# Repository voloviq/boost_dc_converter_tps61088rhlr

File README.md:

# boost_dc_converter_tps61088rhlr

Development Board of TPS61088 Boost DC-DC Converter

Board 3D view

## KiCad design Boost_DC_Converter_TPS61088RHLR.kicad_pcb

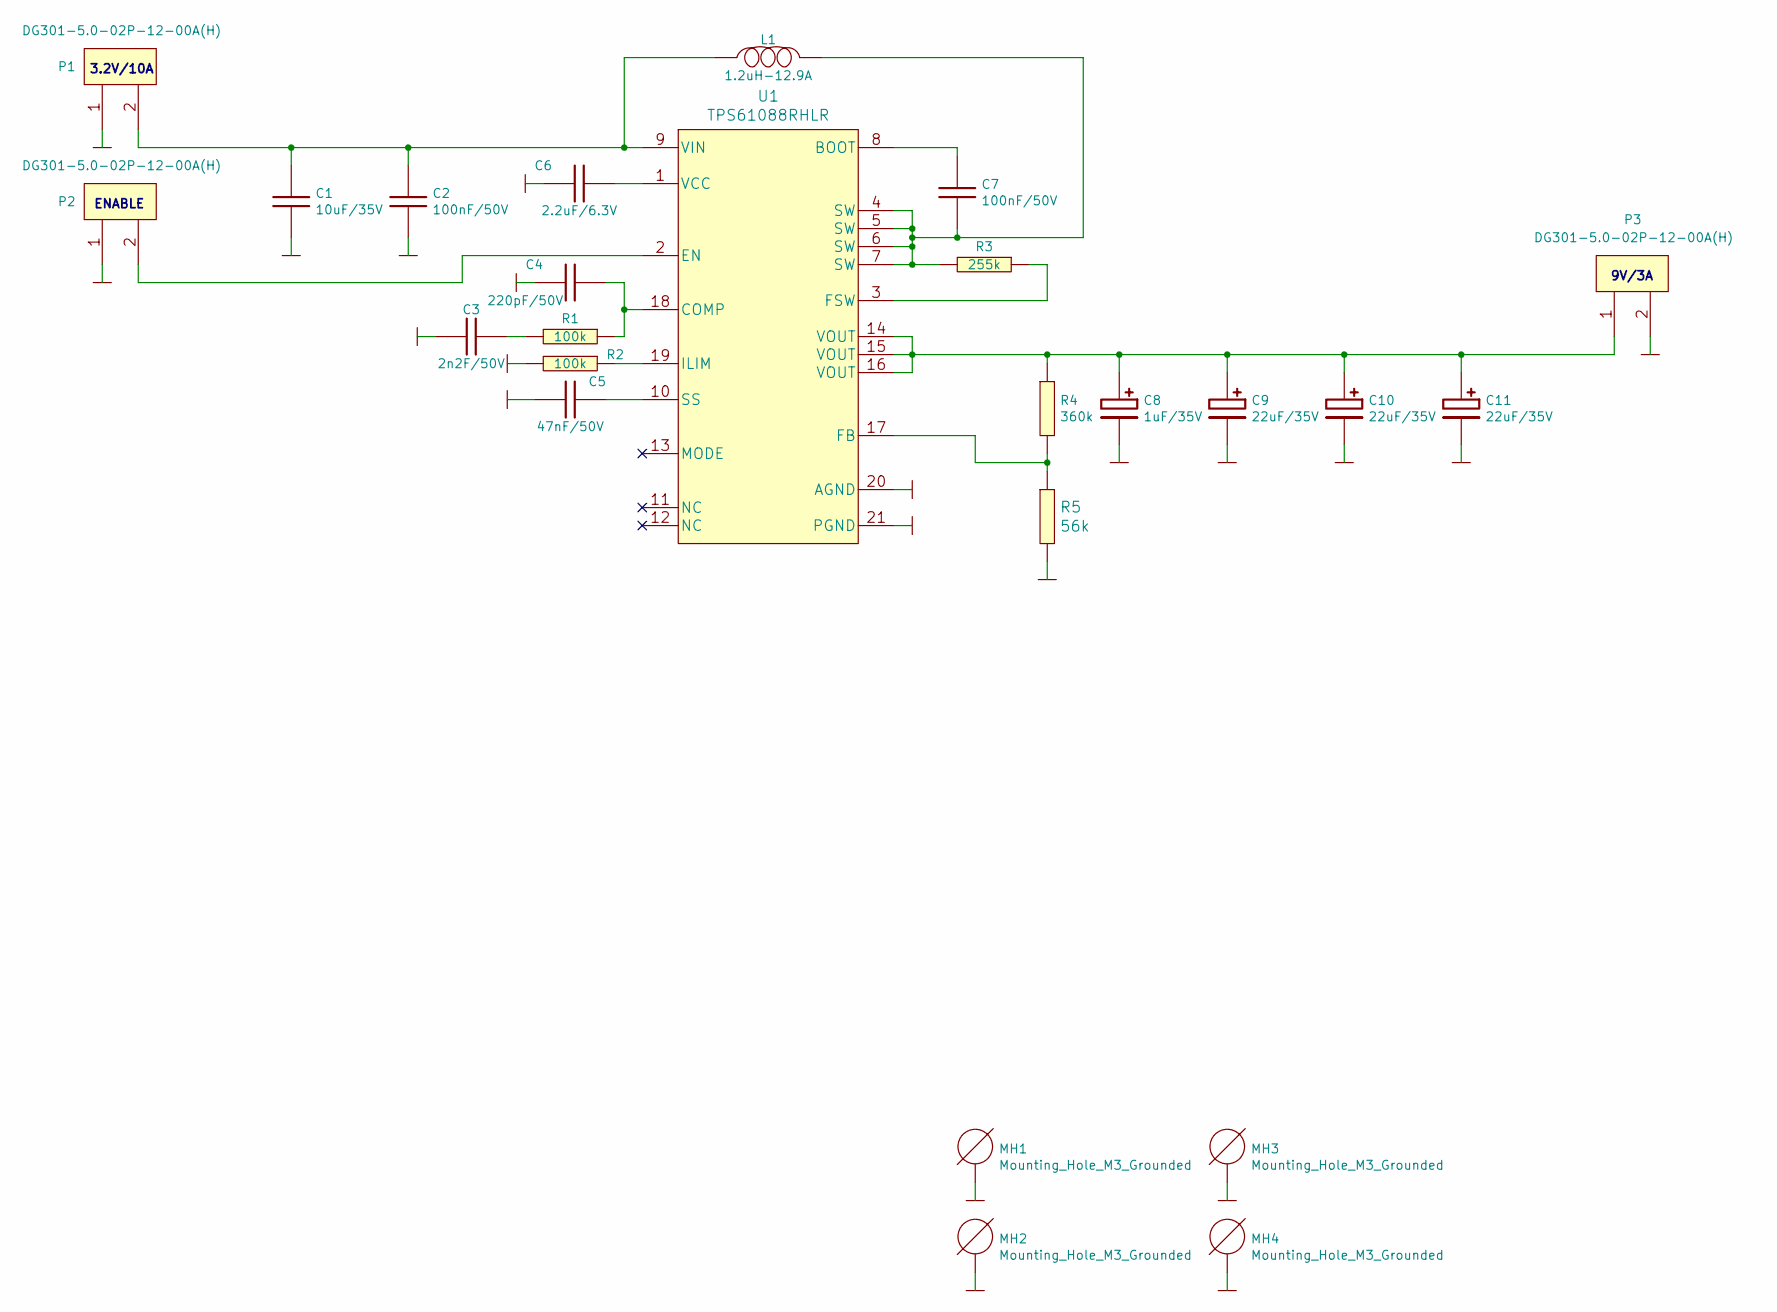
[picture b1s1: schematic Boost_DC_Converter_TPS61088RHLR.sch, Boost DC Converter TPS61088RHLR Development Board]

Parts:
C1: 10uF/35V; 10uF_35V_X7R_1210; Manufacturer Part Number CL32B106KLULNNE
C2, C7: 100nF/50V; 100nF_0603; Manufacturer Part Number CL10B104JB8NNNC
C3: 2n2F/50V; 2.2nF_0603; Manufacturer Part Number GRM1885C1H222JA01D
C4: 220pF/50V; 220pF_0603; Manufacturer Part Number 06035A221JAT2A; LCSC Part # (optional) C431002
C5: 47nF/50V; 47nF_0603; Manufacturer Part Number 0603B473K500CT; LCSC Part # (optional) C313102
C6: 2.2uF/6.3V; 2_2uF_0603
C8: 1uF/35V; 1uF_35V_B_Tantal
C9, C10, C11: 22uF/35V; 22uF_35V_Size_D; Manufacturer Part Number 293D226X9035D2TE3; LCSC Part # (optional) C126947
L1: 1.2uH-12.9A; CDMC8D28NP-1R2MC; Manufacturer Part Number CDMC8D28NP-1R2MC
MH1, MH2, MH3, MH4: Mounting_Hole_M3_Grounded
P1, P2, P3: DG301-5.0-02P-12-00A(H); Manufacturer Part Number DG301-5.0-02P-12-00A(H)
R1, R2: 100k; 100k_0603; Manufacturer Part Number HP03W5J0104T5E; LCSC Part # (optional) C269699
R3: 255k; 255k_0603; Manufacturer Part Number ERA3AEB2553V; LCSC Part # (optional) C23354
R4: 360k; 360k_0603
R5: 56k; 56k_0603; Manufacturer Part Number 0603SAF5602T5E
U1: TPS61088RHLR; Manufacturer Part Number TPS61088RHLR

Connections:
GND: C1.2, C2.2, C3.2, C4.2, C5.2, C6.2, C8.2, C9.2, C10.2, C11.2, MH1.1, MH2.1, MH3.1, MH4.1, P1.1, P2.1, P3.2, R2.2, R5.2, U1.20 (AGND), U1.21 (PGND)
unnamed: C1.1, C2.1, L1.1, P1.2, U1.9 (VIN)
unnamed: C3.1, R1.2
unnamed: C4.1, R1.1, U1.18 (COMP)
unnamed: C5.1, U1.10 (SS)
unnamed: C6.1, U1.1 (VCC)
unnamed: C7.1, U1.8 (BOOT)
unnamed: C7.2, L1.2, R3.2, U1.4 (SW), U1.5 (SW), U1.6 (SW), U1.7 (SW)
unnamed: C8.1, C9.1, C10.1, C11.1, P3.1, R4.1, U1.14 (VOUT), U1.15 (VOUT), U1.16 (VOUT)
unnamed: P2.2, U1.2 (EN)
unnamed: R2.1, U1.19 (ILIM)
unnamed: R3.1, U1.3 (FSW)
unnamed: R4.2, R5.1, U1.17 (FB)

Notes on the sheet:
9V/3A
ENABLE
3.2V/10A

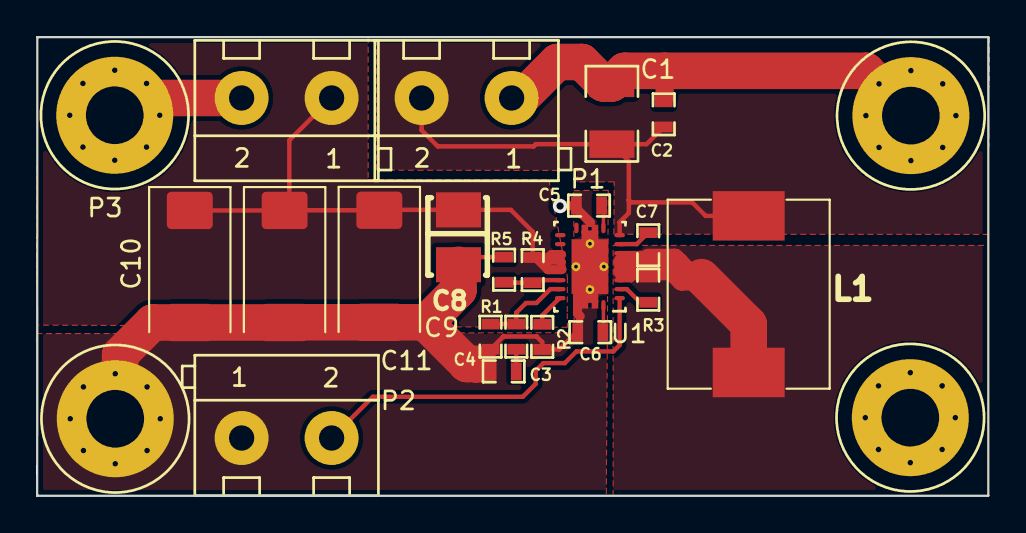
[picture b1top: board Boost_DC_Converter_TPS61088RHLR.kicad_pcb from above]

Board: 2 copper layers, 52.8 x 25.5 mm, 25 parts (0 on the bottom side), 13 nets.

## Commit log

2020-11-26 Initial
2020-11-26 Schematic done
2020-11-27 PCB almost done
2020-11-28 Added all tracks on pcb, problem with zones
2020-12-10 Generated gerbers and schematic BOM
2020-12-10 Removed some backup file
